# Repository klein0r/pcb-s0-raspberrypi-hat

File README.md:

# S0 RaspberryPi Hat

[Gerber-Files](https://github.com/klein0r/pcb-s0-raspberrypi-hat/releases)

## Preview

## License

The MIT License (MIT)

Copyright (c) 2026 Matthias Kleine <info@haus-automatisierung.com>

Permission is hereby granted, free of charge, to any person obtaining a copy
of this software and associated documentation files (the "Software"), to deal
in the Software without restriction, including without limitation the rights
to use, copy, modify, merge, publish, distribute, sublicense, and/or sell
copies of the Software, and to permit persons to whom the Software is
furnished to do so, subject to the following conditions:

The above copyright notice and this permission notice shall be included in
all copies or substantial portions of the Software.

THE SOFTWARE IS PROVIDED "AS IS", WITHOUT WARRANTY OF ANY KIND, EXPRESS OR
IMPLIED, INCLUDING BUT NOT LIMITED TO THE WARRANTIES OF MERCHANTABILITY,
FITNESS FOR A PARTICULAR PURPOSE AND NONINFRINGEMENT. IN NO EVENT SHALL THE
AUTHORS OR COPYRIGHT HOLDERS BE LIABLE FOR ANY CLAIM, DAMAGES OR OTHER
LIABILITY, WHETHER IN AN ACTION OF CONTRACT, TORT OR OTHERWISE, ARISING FROM,
OUT OF OR IN CONNECTION WITH THE SOFTWARE OR THE USE OR OTHER DEALINGS IN
THE SOFTWARE.

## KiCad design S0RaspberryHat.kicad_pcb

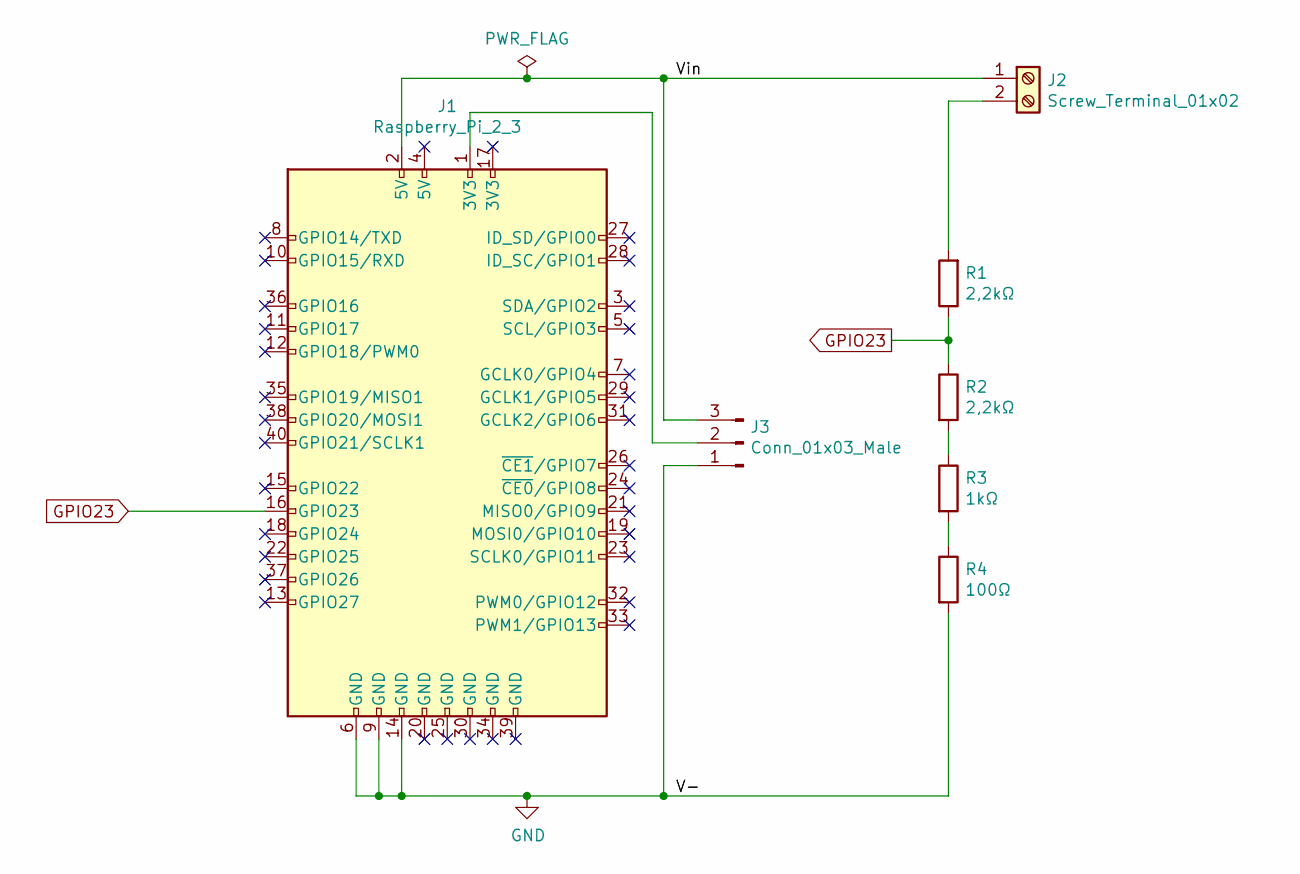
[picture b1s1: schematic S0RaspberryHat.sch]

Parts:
J1: Raspberry_Pi_2_3; PinHeader_2x08_P2.54mm_Vertical
J2: Screw_Terminal_01x02; TerminalBlock_bornier-2_P5.08mm
J3: Conn_01x03_Male; PinHeader_1x03_P2.54mm_Vertical
R1, R2: 2,2kΩ; R_Axial_DIN0207_L6.3mm_D2.5mm_P10.16mm_Horizontal
R3: 1kΩ; R_Axial_DIN0207_L6.3mm_D2.5mm_P10.16mm_Horizontal
R4: 100Ω; R_Axial_DIN0207_L6.3mm_D2.5mm_P10.16mm_Horizontal

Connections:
/Vin: J1.2 (5V), J2.1, J3.3
GND: J1.6 (GND), J1.9 (GND), J1.14 (GND), J3.1, R4.2
GPIO23: J1.16 (GPIO23), R1.1, R2.1
unnamed: J1.1 (3V3), J3.2
unnamed: J2.2, R1.2
unnamed: R2.2, R3.1
unnamed: R3.2, R4.1

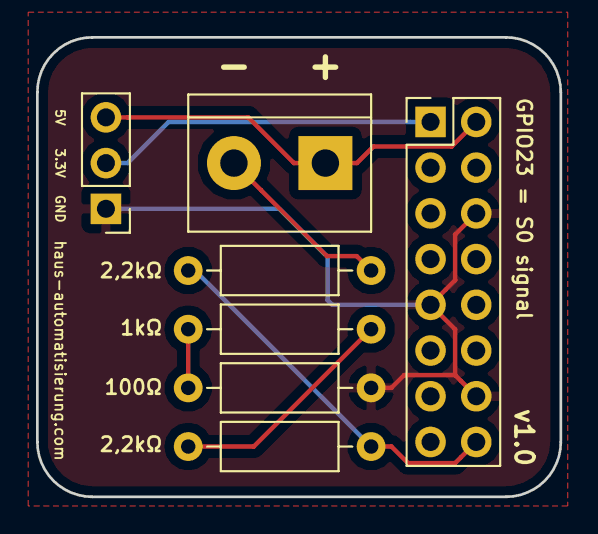
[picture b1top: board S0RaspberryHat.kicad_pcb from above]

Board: 2 copper layers, 29.1 x 25.5 mm, 7 parts (0 on the bottom side), 7 nets.

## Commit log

2019-04-18 v1.0
2019-04-18 Readme and license
2022-01-30 Update LICENSE
2026-01-28 Year 2026
